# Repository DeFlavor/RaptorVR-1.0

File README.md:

# RaptorVR 1.0

RaptorVR 1.0 is a **prototype** SlimeVR carrier and enclosure for the **ELEGOO ESP-WROOM-32 USB-C 30-pin development board** and the **SlimeVR MuMo V1.1 ICM-45686 + QMC6309 breakout**. Its rounded outline, clear assembly zones, paired 1N5817 charge diodes, through-hole construction, and 50 mm strap chassis are inspired by the meowCarrier approach while using a larger ESP32-specific layout.

## Important status

This package passed automated geometry, copper-clearance, Gerber-parsing, and watertight-mesh checks. It has **not** been fabricated or electrically bench-tested. Treat revision 0.12 as a prototype and inspect it in a Gerber viewer before ordering.

## Supported parts

- ELEGOO ESP-WROOM-32 USB-C, 30 pins, two 15-pin rows on 2.54 mm pitch and 25.4 mm row spacing.
- MuMo V1.1, 18 x 13 mm, 1.2 mm thick, with both the seven-pin `J1 TOP_PINS` edge and six-pin `J2 BOTTOM_PINS` edge fitted.
- Protected TP4056 USB-C single-cell charger module, nominally 26 x 17 mm, with `IN+`, `IN-`, `B+`, `B-`, `OUT+`, and `OUT-` pads.
- Two axial 1N5817 Schottky diodes.
- 180 kOhm, 220 kOhm, and 100 kOhm 1/4 W resistors. The three-resistor divider matches the current SlimeVR `BOARD_WROOM32` defaults and feeds GPIO36/VP.
- SK12D07/SK12D07VG high-3mm SPDT slide switch.
- One protected 3.7 V, one-cell LiPo up to approximately 64 x 42 x 12 mm. The confirmed 1500 mAh battery measures 52 x 30.5 x 11 mm and fits with clearance.
- One adjustable 50 mm (2-inch) elastic or nylon body strap, 1.0-2.0 mm thick, with a side-release buckle or hook-and-loop adjustment.

## JLCPCB files

Upload [`hardware/pcb/RaptorVR_1_0_JLCPCB_Gerbers.zip`](hardware/pcb/RaptorVR_1_0_JLCPCB_Gerbers.zip) directly to JLCPCB. Recommended prototype settings:

- 2 layers, 86.36 x 53.34 mm
- 1.0 mm FR-4
- Purple solder mask for the shown style, or green for the quickest fabrication
- Lead-free HASL
- 1 oz copper
- Remove order number: specify the bottom `JLCJLCJLCJLC` location if the ordering interface supports it

The design is through-hole/module assembled. `BOM.csv` is a purchasing list; `CPL.csv` intentionally contains no SMT placement data.

## MuMo and firmware wiring

The PCB is SPI-first:

| Signal | ESP32 | MuMo |
| --- | --- | --- |
| SCLK | GPIO18 | J1.4 SCL |
| MOSI | GPIO23 | J1.5 SDA |
| MISO | GPIO19 | J1.7 SDO |
| CS | GPIO5 | J1.6 CS |
| INT1 | GPIO17 | J2.3 INT1 |
| Power | 3V3 | J1.2 3V3 |
| Ground | GND | J1.3 GND |

The same SCL/SDA wires can be used for I2C if the MuMo jumpers are configured according to its official instructions. For SPI, use a custom SlimeVR build with the pins above and ICM-45686 selected. Do not assume a generic prebuilt WROOM32 image has this exact custom SPI map.

Battery monitoring uses GPIO36/VP and these firmware values, in kOhm:

```cpp
#define PIN_BATTERY_LEVEL 36
#define BATTERY_SHIELD_RESISTANCE 180
#define BATTERY_SHIELD_R2 220
#define BATTERY_SHIELD_R1 100
```

## Enclosure

Creality Print can import the STL files in `hardware/enclosure/`:

- `RaptorVR_1_0_case_50mm_strap`: rounded chassis with ESP32 USB-C, charger USB-C, switch openings, four reinforced screw bosses, and two reinforced underside rails rotated so its 92 mm long side is vertical when worn with a 50 mm body strap.
- `RaptorVR_1_0_battery_separator_tray`: full insulating barrier between the LiPo and PCB, with PCB standoffs and a small wire slot.
- `RaptorVR_1_0_screw_lid_M3`: positively retained lid with four 3.4 mm M3 clearance holes, a 0.20 mm-per-side alignment plug, and the centered raised RaptorVR logo.
- `RaptorVR_1_0_chassis_assembled.glb` and `RaptorVR_1_0_chassis_exploded.glb`: accurate colored models for interactive orbit and zoom viewing.

The complete supplied logo image is traced directly into the lid—raptor mark, original lettering shapes, spacing, and the original `RAPTOR`/`VR` two-line arrangement. No substitute font is used. The artwork is scaled uniformly to 54 mm wide and embossed 0.8 mm above the lid for clear resin and FDM visibility. For a contrasting FDM logo, add a filament change for the final four 0.20 mm layers; a single-color print also works. For resin, angle the lid approximately 20-30 degrees and place supports on the inside face so the raised logo remains clean.

Use four **M3 x 10 mm thread-forming/self-tapping pan-head screws for plastic**. The case has 2.6 mm blind pilot holes, so the screw tips cannot reach the PCB or battery. Tighten only until the lid is seated; overtightening can strip printed threads. Do not use screws longer than 10 mm unless you first verify the remaining boss depth.

For vertical body mounting, thread one **50 mm (2-inch) elastic or nylon strap** beneath both underside rails, then add an adjustable side-release buckle or hook-and-loop closure. The rails are turned 90 degrees from the earlier layout: the strap travels across the 60 mm short side, leaving the 92 mm long side vertical on your body. The passages are 50.5 mm wide and 2.2 mm high. Round or lightly sand any sharp printed edges before installing the strap, leave enough slack for comfortable movement and circulation, and inspect the strap and rails before each use. Do not resin-print the flexible strap itself.

Starting Creality settings: 0.4 mm nozzle, 0.20 mm layers, four walls, five top/bottom layers, 35% gyroid infill, PLA+ or PETG. Print the case upright, the separator flat, and the lid with its large outer face on the build plate. If your printer runs tight, scale only the lid X/Y to 100.2% or lightly sand the alignment plug.

## Assembly safety

1. Do not attach the LiPo until every other part is soldered and inspected.
2. Verify `BAT+` and `BAT-` with a multimeter. Reversed LiPo polarity can cause fire.
3. Use only a protected one-cell LiPo and a TP4056 board that includes battery protection.
4. Confirm the TP4056 pad order against its seller diagram; visually similar boards can differ.
5. Check for shorts from `SYS_5V` to ground and from `3V3` to ground before inserting the ESP32 or MuMo.
6. The striped end of each 1N5817 goes to the PCB pad marked `K`.
7. Use USB-A-to-USB-C for inexpensive TP4056 modules unless the module explicitly supports USB-C-to-C charging.
8. Never charge an unattended or damaged LiPo, and do not wear the tracker while charging.

## Source and regeneration

- Editable PCB layout: `hardware/pcb/source/RaptorVR_1_0.kicad_pcb`
- Dimension-controlled generator: `hardware/pcb/source/generate_project.py`
- Supplied logo reference: `hardware/pcb/source/assets/RaptorVR_logo_reference.png`
- Human-readable schematic: `hardware/pcb/schematic/RaptorVR_1_0_schematic.pdf`
- Validation report: `VALIDATION.json`

Regenerate with Python 3.12 plus `numpy`, `Pillow`, `shapely`, `trimesh`, `manifold3d`, `matplotlib`, `reportlab`, and `gerbonara`.

## References and attribution

- meowCarrier by Shine Bright (MIT): https://github.com/Shine-Bright-Meow/meowCarrier
- SlimeVR tracker documentation: https://docs.slimevr.dev/diy/tracker-schematics.html
- Official MuMo V1.1 schematic: https://docs.slimevr.dev/files/mumo-schematic-1.1.pdf
- SlimeVR firmware: https://github.com/SlimeVR/SlimeVR-Tracker-ESP

The RaptorVR 1.0 scripts, PCB layout, documentation, and enclosure geometry are released under the MIT License. Third-party modules and reference projects retain their original licenses.

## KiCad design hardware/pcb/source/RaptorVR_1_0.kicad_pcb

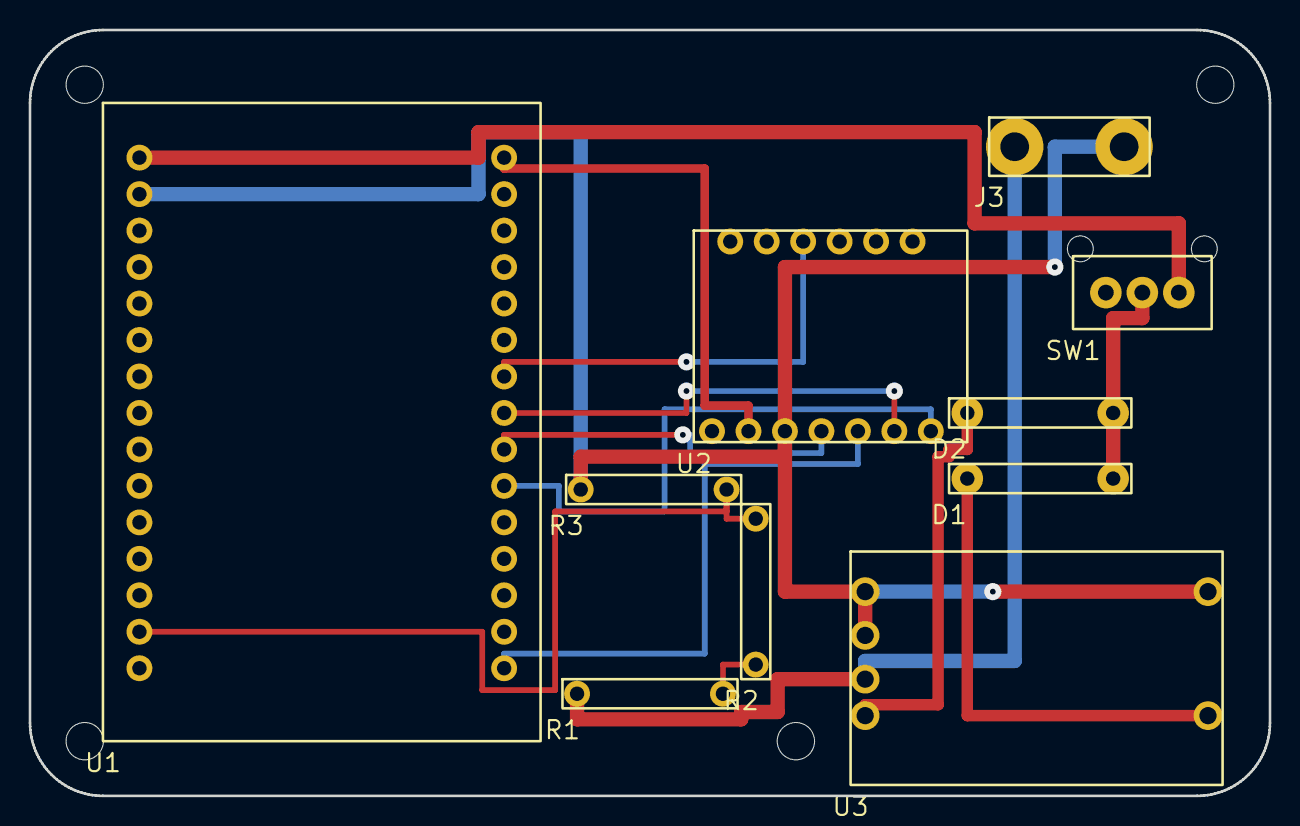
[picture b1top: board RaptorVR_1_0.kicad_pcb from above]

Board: 2 copper layers, 86.4 x 53.3 mm, 10 parts (0 on the bottom side), 14 nets.

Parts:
D1: 1N5817; D1
D2: 1N5817; D2
J3: LiPo wire pads; J3
R1: 180k 1/4W; R1
R2: 220k 1/4W; R2
R3: 100k 1/4W; R3
SW1: SK12D07VG3 high-3mm; SW1
U1: ELEGOO ESP-WROOM-32 USB-C 30-pin; U1
U2: MuMo V1.1 ICM-45686 + QMC6309; U2
U3: TP4056 USB-C protected module; U3

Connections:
3V3: U1.R1, U2.2
ADC_BAT: R2.2, R3.2, U1.L14
BAT+: J3.+, R1.1, U3.5
CHG_OUT: D2.1, U3.6
CS: U1.R8, U2.6
DIV_A: R1.2, R2.1
GND: J3.-, R3.1, U1.L2, U2.3, U3.2, U3.4, U3.7
INT1: U1.R7, U2.3
MISO: U1.R10, U2.7
MOSI: U1.R15, U2.5
PWR_OR: D1.2, D2.2, SW1.2
SCLK: U1.R9, U2.4
SYS_5V: SW1.3, U1.L1
USB_IN: D1.1, U3.1

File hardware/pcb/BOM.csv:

Reference,Qty,Value / Part,Footprint / Notes,Assembly
U1,1,ELEGOO ESP-WROOM-32 USB-C 30-pin,"2x15, 2.54 mm pitch, 25.4 mm row spacing",Socket or solder headers
U2,1,SlimeVR MuMo V1.1 ICM-45686 + QMC6309,"18 x 13 mm, 7+6 castellated/header pins",Fit both rows for SPI
U3,1,Protected TP4056 USB-C module,Approx. 26 x 17 mm; IN+/IN-/B+/B-/OUT+/OUT-,Protection version required
"D1,D2",2,1N5817 Schottky diode,"DO-41 axial, 10.16 mm pitch",Band/cathode toward K
R1,1,180 kOhm 1/4 W,"Axial, 10.16 mm pitch",Battery sense
R2,1,220 kOhm 1/4 W,"Axial, 10.16 mm pitch",Battery divider upper
R3,1,100 kOhm 1/4 W,"Axial, 10.16 mm pitch",Battery divider lower
SW1,1,SK12D07/SK12D07VG high-3mm,"SPDT, 2.54 mm pin pitch",Center common
J3,1,503759 3.7 V protected LiPo,Bare red/black leads to large pads,Verify polarity before soldering
Headers,1,2.54 mm male/female header assortment,"For ESP32, MuMo, TP4056",Trim flush under PCB

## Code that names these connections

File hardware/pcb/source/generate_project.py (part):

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
    # ELEGOO ESP-WROOM-32 USB-C 30-pin board. USB-C faces the lower board edge.
    left_names = [
        ("VIN", "SYS_5V"), ("GND", "GND"), ("GPIO13", "NC"), ("GPIO12", "NC"),
        ("GPIO14", "NC"), ("GPIO27", "NC"), ("GPIO26", "NC"), ("GPIO25", "NC"),
        ("GPIO33", "NC"), ("GPIO32", "NC"), ("GPIO35", "NC"), ("GPIO34", "NC"),
        ("GPIO39", "NC"), ("GPIO36", "ADC_BAT"), ("EN", "NC"),
    ]
    right_names = [
        ("3V3", "3V3"), ("GPIO15", "NC"), ("GPIO2", "NC"), ("GPIO0", "NC"),
        ("GPIO4", "NC"), ("GPIO16", "NC"), ("GPIO17", "INT1"), ("GPIO5", "CS"),
        ("GPIO18", "SCLK"), ("GPIO19", "MISO"), ("GPIO21", "NC"), ("RX0", "NC"),
        ("TX0", "NC"), ("GPIO22", "NC"), ("GPIO23", "MOSI"),
    ]
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
    # Common protected TP4056 USB-C module (about 26 x 17 mm). USB-C faces right.
    tp = [
        Pad("U3", "1", mm(323), mm(188), "USB_IN", 2.00, 1.20, label="IN+"),
        Pad("U3", "2", mm(323), mm(154), "GND", 2.00, 1.20, label="IN-"),
        Pad("U3", "4", mm(229), mm(166), "GND", 2.00, 1.20, label="B-"),
        Pad("U3", "5", mm(229), mm(178), "BAT+", 2.00, 1.20, label="B+"),
        Pad("U3", "6", mm(229), mm(188), "CHG_OUT", 2.00, 1.20, label="OUT+"),
        Pad("U3", "7", mm(229), mm(154), "GND", 2.00, 1.20, label="OUT-"),
    ]
    components.append(Component("U3", "TP4056 USB-C protected module", "6-pad single-cell Li-ion charger/protection module", (mm(225), mm(143), mm(327), mm(207)), tp))
    pads.extend(tp)

    # Axial 1N5817 diodes, cathodes toward the power-OR node.
    d1 = [Pad("D1", "1", mm(257), mm(123), "USB_IN", 2.20, 1.00, label="A"), Pad("D1", "2", mm(297), mm(123), "PWR_OR", 2.20, 1.00, label="K")]
    d2 = [Pad("D2", "1", mm(257), mm(105), "CHG_OUT", 2.20, 1.00, label="A"), Pad("D2", "2", mm(297), mm(105), "PWR_OR", 2.20, 1.00, label="K")]
    components.extend([
        Component("D1", "1N5817", "USB-to-load Schottky diode", (mm(252), mm(119), mm(302), mm(127)), d1),
        Component("D2", "1N5817", "battery-to-load Schottky diode", (mm(252), mm(101), mm(302), mm(109)), d2),
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    pads.extend(d1 + d2)

    # Battery divider matching SlimeVR BOARD_WROOM32 defaults: 180k + 220k over 100k.
    r180 = [Pad("R1", "1", mm(150), mm(182), "BAT+", label="BAT+"), Pad("R1", "2", mm(190), mm(182), "DIV_A", label="DIV_A")]
    r220 = [Pad("R2", "1", mm(199), mm(174), "DIV_A", label="DIV_A"), Pad("R2", "2", mm(199), mm(134), "ADC_BAT", label="ADC")]
    r100 = [Pad("R3", "1", mm(151), mm(126), "GND", label="GND"), Pad("R3", "2", mm(191), mm(126), "ADC_BAT", label="ADC")]
    components.extend([
        Component("R1", "180k 1/4W", "battery sense series resistor", (mm(146), mm(178), mm(194), mm(186)), r180),
        Component("R2", "220k 1/4W", "battery sense upper divider resistor", (mm(195), mm(130), mm(203), mm(178)), r220),
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    # SK12D07/SK12D07VG. Center common, right pad ON; left pad unused/OFF.
    sw = [
        Pad("SW1", "1", mm(295), mm(72), "NC", 2.20, 1.10, label="OFF"),
        Pad("SW1", "2", mm(305), mm(72), "PWR_OR", 2.20, 1.10, label="COM"),
        Pad("SW1", "3", mm(315), mm(72), "SYS_5V", 2.20, 1.10, label="ON"),
    ]
    components.append(Component("SW1", "SK12D07VG3 high-3mm", "SPDT slide power switch", (mm(286), mm(62), mm(324), mm(82)), sw))
    pads.extend(sw)
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            ("SPI MOSI / I2C SDA", "GPIO23", "J1.5 SDA", "Same wire can be I2C SDA"),
            ("SPI MISO", "GPIO19", "J1.7 SDO", "Used in SPI mode"),
            ("SPI CS", "GPIO5", "J1.6 CS", "Used in SPI mode"),
            ("Interrupt", "GPIO17", "J2.3 INT1", "Custom firmware pin"),
            ("Battery ADC", "GPIO36 / VP", "-", "180k + 220k over 100k divider"),
            ("Module power", "3V3", "J1.2 3V3", "Do not power MuMo from 5V"),
            ("Ground", "GND", "J1.3 GND", "Common ground"),
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    block(0.7, 5.6, 4.1, 3.0, "U1 - ELEGOO ESP32", "ESP-WROOM-32 USB-C, 30 pin")
    block(6.1, 5.6, 4.0, 3.0, "U2 - MuMo V1.1", "3V3 J1.2 - GND J1.3")
    block(11.6, 5.6, 3.5, 3.0, "Battery sense", "")
    for i, (name, y) in enumerate([("GPIO18 SCLK", 8.05), ("GPIO23 MOSI", 7.55), ("GPIO19 MISO", 7.05), ("GPIO5 CS", 6.55), ("GPIO17 INT1", 6.05)]):
        wire([(4.8, y), (6.1, y)], name.split()[1])
    ax.text(8.1, 5.25, "SPI preferred; bridge MuMo JP1-JP4 for I2C", ha="center", fontsize=8, color="#7c3aed")

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| MOSI | GPIO23 | J1.5 SDA |
| MISO | GPIO19 | J1.7 SDO |
| CS | GPIO5 | J1.6 CS |
| INT1 | GPIO17 | J2.3 INT1 |
| Power | 3V3 | J1.2 3V3 |
| Ground | GND | J1.3 GND |

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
